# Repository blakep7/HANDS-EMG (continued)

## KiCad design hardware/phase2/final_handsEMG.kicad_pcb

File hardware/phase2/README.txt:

How to add components to our hands-emg-lib

1. Download the following from Ultra Librarian (https://app.ultralibrarian.com/)
	- Symbol (.kicad_sym)
	- Footprint (.kicad_mod) (Ignore the -L or -M footprints, use the normal one)
	- 3D Model (.stp or .step)
	* My typical download process
		* 3D CAD Model: Check STEP
		* KiCAD: Check KiCAD v6+
		* Symbol Pin Ordering: Designers preference, read the (i) to understand what this is.
		  Download both and compare to see which one would make a cleaner schematic.
		* Footprint Units: Metric (mm)
	
1b. If you cannot find the component on Ultra Librarian, check Component Search Engine (https://componentsearchengine.com/)
	- Don't mix and match symbols and footprints from different websites
	- If you cant find the components 3d model on ultralibrarian, its fine to download the 3d model from component search engine and attach to footprint from ultralibrarian.
	
1c. After downloading all the files it will be a zip do the following
	- Extract the zip to some folder on your PC.
	- Rename all the files to be the same name (typically part number)
	  Heres an example before and after with the ADS1299 from Ultra Librarian
			Before: 2025-03-01_06-35-12.kicad_sym
					PAG0064A.stp
					PAG64_TEX.kicad_mod
					
			After:  ADS1299-4PAGR.kicad_sym
					ADS1299-4PAGR.stp
					ADS1299-4PAGR.kicad_mod
	
2. Copy the 3d model file from the download into the hands-emg-lib.3dshapes.

3. Import the footprint
	- Open the KiCad Footprint Editor
	- Filter hands-emg-lib
	- Right click hands-emg-lib
	- Import Footprint
	- Select the footprint file from the download
	- Open the footprints properties menu
		- Check the "Value" and confirm its the proper manufacturer's part number (if you had to rename footprint file then it's likely incorrect)
		- Add a description of what it is (typically not part number, the description helps to search the part)
		- Go to the 3D model tab
		- Click the little folder icon to add 3d model
		- Select the 3d model file in the hands-emg-lib.3dshapes folder
		- Rotate/Offset model to fit the footprint (scaling is needed in very few cases)
	- Click OK to close the footprint properties menu
	- File -> Save
	- Dont change the name, filter for hands-emg-lib, click hands-emg-lib, click OK.
	
4. Import the symbol
	- Open the KiCad Symbol Editor
	- Filter hands-emg-lib
	- Right click hands-emg-lib
	- Import Symbol
	- Select the symbol file from the download
	- Open the symbol properties menu
		- Click on footprint
		- Click on the little books icon to open the "footprint chooser"
		- Filter for hands-emg-lib
		- Select the footprint imported in step 3 under hands-emg-lib (for this component)
		- Click OK
		- Add datasheet link under "Datasheet" field
		- Add description
		- Create new field
			- Click '+' symbol
			- Name this field procurement
			- Make sure to un-check the show column for this field
			- Provide purchase link for this component
				- Try to keep it all from DigiKey
				- No obsolete parts, no limited stock, must be immediately aviable, no lead time
		- Click OK to close symbol properties menu
	- File -> Save
	
5. Commit these changes to git and push so we all have easy access to the components.

6. Use your imported component. (Seach for hands-emg-lib in symbol/footprint selection menu when placing)

7. You can delete the downloaded files from your downloads folder, importing them has copied them all to our project.

Note! This library is 'project' scoped, there is no need to edit any of your kicad settings to use it. It will not be aviable in other projects.

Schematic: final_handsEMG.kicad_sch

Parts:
C1: 10uF; CAPC1608X90N
C2: 100uF; CAP_CC1206_YAG
C3, C9, C11, C26, C34: CKCL44X7R1H102M085AA; CAPCAF50P200X125X85-8; PARTREV Dec 2014
C5, C12, C13, C15, C24, C28: 0.1uF; YAG_CC0402_YAG
C6, C7, C14, C17, C18, C19, C21, C22, C27: 1uF; CAP_CC0402KRX7R5BB105_YAG
C16: 1nF; YAG_CC0402_YAG
C45, C46, C50, C51, C60, C61, C65, C66: 10uF; CAPC2012X95N
C47, C48, C49, C58, C62: 1uF; CAPC1608X90N
C57: 0.1uF; CAPC1608X90N
C59, C63, C64: 2.2uF; CAP_GRM18_MUR
C67: 0.01uF; CAPC1608X90N
D2, D3, D4, D5, D6, D7: TPD4E1B06DCKR; DCK6_TEX
J1: Conn_02x13_Odd_Even; AMPHENOL_68021-226HLF
L1, L2, L4, L5: 3.3uH; INDC2012X87N
R1, R2, R3, R4, R6: 2.2K; CAY16_BRN
R5: 1M; RC0402N_YAG
SWD1: FTSH-107-01-L-DV-K; CON14_2X7_DUK_FTSH_SAI
TP1: RAW; KEYSTONE_5000
TP2: LDO3V3; KEYSTONE_5000
TP4: +3V3; KEYSTONE_5000
TP5: -5V; KEYSTONE_5001
TP6: +5V; KEYSTONE_5001
TP7: +2V5; KEYSTONE_5001
TP8: -2V5; KEYSTONE_5001
U1: ADS1299CPAG; QFP64P50_1200X1200X120L60X22N
U2: STM32L496ZGT6; LQFP144-20x20mm_STM; PARTREV 10
U3: LTC3586EUFE-3-PBF; QFN-38_UFE_LIT
U4: FT231XQ-R; QFN20_FT231XQ_FTD
U6: TPS60403DBVT; SOT95P280X145-5N
U8: TPS72325DBVT; SOT95P280X145-5N
U9: TPS73225DBVT; SOT95P280X145-5N
dC1: 0.01uF; CC0402N_YAG
dC2, dC3: 47pF; G-033_MUR
dD3: D_Small; SOD882_STM
dD4: RED; LED_LTST-C191KRKT_LTO
dD5: GREEN; LED_LTST-C191KGKT_LTO
dF1: Fuse_Small; FUSE_F050-2
dL2: L_Small; IND_1005_TDK
dR1, dR2: 27; RC0402N_YAG
dR3, dR4: 330; RC0402N_YAG
dR6, dR7: 1K; RC0402N_YAG
pC1, pC4, pC5, pC8, pC9, pC11: 1uF; C1005X5R0J105M
pC2: 10uF; GRM21BR61A106KE19
pC3: 10uF; GRM21BR61A106KE19L
pC6, pC7, pC19: 22uF; JMK212BJ226MG-T
pC10: 2.2uF; C1608X5R0J225M
pC12, pC21, pC23: 10uF; C1608X5R0J106M
pC13: 100uF; GRM31CR60J107ME39L
pC14: 47uF; LMK316BJ476ML-T
pC15, pC20, pC22, pC24: 10pF; 04025A100KAT
pC16, pC28, pC29: 0.1uF; C1005X5R1C104K
pC17: 330pF; 04025A331KAT
pC18: 33pF; 04025A330KAT
pD2: GREEN (CHRG); LED-0603
pD3: RED (FAULT); LED-0603
pL1: 3.3uH; LPS4018-332MLC
pL2, pL3: 2.2uH; LPS4018-222MLC
pL4, pL5: 4.7uH; IND_LPS4018-472MRC
pQ1: PMOS; SI2333DS
pR2, pR29, pR30, pR31: 1; CRCW04021R00JNED
pR3, pR9: 100K; CRCW0402100KFKED
pR4, pR10, pR12: 0; CRCW04020000Z0EDC
pR5, pR7: 1K; CRCW04021K00JNED
pR6, pR8: 2.2K; CRCW04022K20FKED
pR13, pR18, pR23, pR26: 20; CRCW040220R0FKED
pR14: 88.7k; CRCW040288K7FKED
pR15: 16.9K; CRCW040216K9FKED
pR16: 3.01K; CRCW04023K01FKED
pR17: 2K; CRCW04022K00FKED
pR19: 15K; CRCW040215K0FKED
pR20: 324K; CRCW0402324KFKED
pR21: 121K; CRCW0402121KFKED
pR22: 105K; CRCW0402105KFKED
pR24: 806K; CRCW0402806KFKED
pR25: 649K; CRCW0402649KFKED
pR27: 232K; CRCW0402232KFKED
pR28: 464K; CRCW0402464KFKED
pR34, pR35, pR80, pR81, pR82, pR83: 10K; CRCW04021K00JNED
sB1: USER; PTS645S_SMTR92_CNK
sB2: RESET; PTS645S_SMTR92_CNK
sC28, sC29, sC30, sC31, sC32, sC33, sC34, sC49, sC50, sC51, sC53, sC57, sC58, sC61: 100nF; CAPC1608X90
sC40: [N/A]; YAG_CC0402_YAG
sC41: 100nF; YAG_CC0402_YAG
sC42: 4.7uF; CAPMP3216X166
sC52, sC54: 4.7uF_X54_0603; CAPC1608X90
sC56, sC59: 1uF; CAPMP3216X166
sC60: 1uF_X5R_0603; CAPC1608X90
sCN14: USB_B_Micro; MOLEX_47589-1001
sD6: ESDALC6V1_1U2; DIODE_ESDALC6V1-1U2
sD10: ESDALC6V1W5; SOT65P210X110-5N; MOUSER_PART_NUMBER 511-ESDALC6V1W5
sJ2: S2B-PH-K-SLFSN; CONN_S2B-PH-K-S_JST
sL3: FerriteBead_Small; FB0603
sLD7: Red; LED-0603
sLD8: Green; LED-0603
sR38, sR52: 10K; RESC1607X60N
sR41, sR43: 330; RESC1607X60N
sR42: 220K; RESC1607X60N
sR44: 100; RESC1607X60N
sR45: 620; RESC1608X55N
sR48: 22K; RESC1607X60N
sR49, sR51: 47K; RESC1608X55
sR54, sR55: 10K (DNP); RESC1607X60N
sT2: 9013; SOT-23
sU12: STMPS2151STR; SOT95P280X145-5N
sU13: USBLC6-2SC6; SOT-23-6

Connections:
1N: D3.4 (IO3), J1.21, R1.1
1P: D2.1 (IO1), J1.22, R1.2
2N: D3.2 (IO2), J1.19, R2.3
2P: D3.5 (IO4), J1.20, R2.4
3N: D4.4 (IO3), J1.17, R2.1
3P: D3.1 (IO1), J1.18, R2.2
3V3OUT: U4.10 (3V3OUT), U4.11 (RESET#), dD4.2 (A), dD5.2 (A)
4N: D4.2 (IO2), J1.15, R3.3
4P: D4.5 (IO4), J1.16, R3.4
5N: D5.4 (IO3), J1.13, R3.1
5P: D4.1 (IO1), J1.14, R3.2
5VCC: C45.1, C46.1, C47.1, C58.1, L1.1, L1.2, TP6.1, U3.6 (VOUT4), U3.7 (VOUT4), U6.2 (IN), U9.1 (IN), U9.3 (EN), pC14.1, pR13.2
6N: D5.2 (IO2), J1.11, R4.3
6P: D5.5 (IO4), J1.12, R4.4
7N: D6.4 (IO3), J1.9, R4.1
7P: D5.1 (IO1), J1.10, R4.2
8N: D6.2 (IO2), J1.7, R6.3
8P: D6.5 (IO4), J1.8, R6.4
*CHRG: U3.30 (*CHRG), pR5.2, pR6.2
*FAULT: U3.38 (*FAULT), pR7.2, pR8.2, pR80.2
-5VCC: C49.1, C50.1, C51.1, C63.1, L2.1, L2.2, TP5.1, U6.1 (OUT), U8.2 (IN), U8.3 (EN)
AVBUS: U3.35 (VBUS), U3.36 (VBUS), dD3.1 (K), dF1.2, pC2.1, pC3.1, pC8.1, pR3.1, sC42.+, sR49.2, sR54.2, sU12.1 (OUT), sU13.5 (VBUS)
AVDD: C13.1, C17.1, C22.1, C24.1, C27.1, C28.1, C57.1, C61.1, D7.2 (IO2), J1.1, J1.2, L5.2, TP7.1, U1.19 (AVDD@1), U1.21 (AVDD@1), U1.22 (AVDD@1), U1.54 (AVDD1), U1.56 (AVDD@1), U1.59 (AVDD@2), U2.32 (VREF+), U2.33 (VDDA), sC56.+, sC57.1, sC58.1, sC59.+, sL3.2
AVIN3: U3.14 (VIN3), pC11.1, pR4.1
AVOUT3: C12.1, C14.1, SWD1.3, TP4.1, U1.48 (DVDD), U1.50 (DVDD), U2.6 (VBAT), U2.17 (VDD), U2.39 (VDD__1), U2.52 (VDD__2), U2.62 (VDD__3), U2.72 (VDD__4), U2.84 (VDD__5), U2.95 (VDDIO2), U2.106 (VDDUSB), U2.108 (VDD__6), U2.121 (VDD__7), U2.131 (VDDIO2__1), U2.144 (VDD__8), U3.16 (VOUT3), U3.17 (VOUT3), U4.12 (VCC), U4.20 (VCCIO), pC19.1, pR18.1, sB1.2, sB1.3, sC28.1, sC29.1, sC30.1, sC31.1, sC32.1, sC33.1, sC34.1, sC49.1, sC50.1, sC51.1, sC52.1, sC53.1, sC54.1, sC60.1, sC61.1, sL3.1, sR41.2, sR44.1, sR45.2, sR51.2, sU12.5 (IN)
AVSS: C1.2, C2.2, C5.2, C6.2, C7.2, C13.2, C15.2, C17.2, C18.1, C19.2, C21.1, C57.2, C66.1, D2.4 (IO3), J1.25, J1.26, L4.2, TP8.1, U1.20 (AVSS@1), U1.23 (AVSS@1), U1.25 (VREFN), U1.32 (AVSS@1), U1.53 (AVSS1), U1.57 (AVSS@1), U1.58 (AVSS@2)
BAT: TP1.1, U3.32 (BAT), pC13.1, pQ1.1 (D), sJ2.1; also elsewhere on the board
BIAS: D7.4 (IO3), J1.5, J1.6, R6.1
BIASIN: C16.2, R5.2, U1.62 (BIASIN), U1.63 (BIASOUT)
BIASINV: U1.61 (BIASINV)
BIASREF: U1.60 (BIASREF)
BIAS_DRV: C16.1, C34.5, R5.1, R6.8
CBUS1: U4.14 (CBUS1), dR4.2
CBUS2: U4.7 (CBUS2), dR3.1
CLK: U1.37 (CLK)
CLKSEL: U1.52 (CLKSEL)
CLPROG: U3.4 (CLPROG), pC16.1, pR16.1
DAISY_IN: U1.41 (DAISY_IN)
DGND: C45.2, C46.2, C47.2, C49.2, C50.2, C51.2, C58.2, C59.2, C60.2, C61.2, C62.2, C63.2, C64.2, C65.2, C66.2, C67.2, SWD1.5, SWD1.7, U1.33 (DGND), U1.49 (DGND), U1.51 (DGND), U2.16 (VSS), U2.30 (VSSA/VREF-), U2.31 (VREF-), U2.38 (VSS__1), U2.51 (VSS__2), U2.61 (VSS__3), U2.71 (VSS__4), U2.83 (VSS__5), U2.94 (VSS__6), U2.107 (VSS__7), U2.120 (VSS__8), U2.130 (VSS__9), U2.143 (VSS__10), U3.39 (EPAD), U4.3 (GND), U4.13 (GND), U4.21 (GND), U6.4 (GND), U8.1 (GND), U9.2 (GND), dC1.2, dC2.2, dC3.2, dD3.2 (A), pC1.2, pC3.2, pC4.2, pC5.2, pC6.2, pC7.2, pC8.2, pC9.2, pC10.2, pC11.2, pC12.2, pC14.2, pC16.2, pC19.2, pC21.1, pC23.1, pC28.2, pC29.2, pR2.2, pR9.1, pR15.1, pR16.2, pR17.2, pR22.2, pR25.2, pR28.2, pR29.1, pR30.1, pR31.1, sB2.2, sB2.3, sC28.2, sC29.2, sC30.2, sC31.2, sC32.2, sC33.2, sC34.2, sC41.2, sC42.-, sC49.2, sC50.2, sC51.2, sC52.2, sC53.2, sC54.2, sC56.-, sC57.2, sC58.2, sC59.-, sC60.2, sC61.2, sCN14.5 (GND), sD6.2 (A), sD10.2 (GND), sJ2.2, sR38.2, sR42.1, sR48.1, sR52.2, sT2.2 (E), sU12.2 (GND), sU13.2 (GND); also elsewhere on the board
DIN: U1.34 (DIN), U2.43 (PA7)
DOUT: U1.43 (DOUT), U2.42 (PA6)
EN1: U2.115 (PD1), U3.21 (EN1)
EN2: U2.116 (PD2), U3.20 (EN2)
EN3: U2.117 (PD3), U3.18 (EN3), pC28.1, pR34.1
EN4: U2.118 (PD4), U3.33 (EN4), pC29.1, pR35.1
FB1: U3.28 (FB1), pC24.1, pR27.2, pR28.1
FB2: U3.23 (FB2), pC22.1, pR24.2, pR25.1
FB3: U3.11 (FB3), pC20.2, pR19.2, pR20.2, pR21.2, pR22.1
FB4: U3.10 (FB4), pC15.2, pR14.1, pR15.2
GATE: U3.31 (GATE), pQ1.2 (G)
GNDA: C3.1, C3.2, C3.3, C3.4, C9.1, C9.2, C9.3, C9.4, C11.1, C11.2, C11.3, C11.4, C12.2, C14.2, C18.2, C21.2, C22.2, C24.2, C26.1, C26.2, C26.3, C26.4, C27.2, C28.2, C34.1, C34.2, C34.3, C34.4, C34.6, D2.3 (GND), D3.3 (GND), D4.3 (GND), D5.3 (GND), D6.3 (GND), D7.1 (IO1), D7.3 (GND), J1.3, J1.4, R6.2, R6.7
GPIO1: U1.42 (GPIO1)
GPIO2: U1.44 (GPIO2)
GPIO3: U1.45 (GPIO3)
GPIO4: U1.46 (GPIO4)
ILIM0: U3.1 (ILIM0), pR81.2
ILIM1: U3.2 (ILIM1), pR82.2
IN1N: C3.5, R1.8, U1.15 (IN1N)
IN1P: C3.6, R1.7, U1.16 (IN1P)
IN2N: C9.7, R2.6, U1.13 (IN2N)
IN2P: C9.8, R2.5, U1.14 (IN2P)
IN3N: C9.5, R2.8, U1.11 (IN3N)
IN3P: C9.6, R2.7, U1.12 (IN3P)
IN4N: C11.7, R3.6, U1.9 (IN4N)
IN4P: C11.8, R3.5, U1.10 (IN4P)
IN5N: C11.5, R3.8, U1.7 (IN5N)
IN5P: C11.6, R3.7, U1.8 (IN5P)
IN6N: C26.7, R4.6, U1.5 (IN6N)
IN6P: C26.8, R4.5, U1.6 (IN6P)
IN7N: C26.5, R4.8, U1.3 (IN7N)
IN7P: C26.6, R4.7, U1.4 (IN7P)
IN8N: C34.7, R6.6, U1.1 (IN8N)
IN8P: C34.8, R6.5, U1.2 (IN8P)
LDO3V3: TP2.1, U3.3 (LDO3V3), pC1.1, pD2.+ (A), pD3.+ (A), pR6.1, pR8.1, pR12.2, pR34.2, pR35.2
MODE: U3.9 (MODE), pR83.2
NRST: SWD1.12, U2.25 (~NRST), sB2.1, sB2.4, sC41.1, sD10.3 (I/02)
NTC: U3.5 (NTC), pR3.2, pR10.2
unnamed: U2.138 (PH3-BOOT0), sR38.1
unnamed: U4.1 (RXD), dR6.2
unnamed: U4.17 (TXD), dR7.2
unnamed: C48.1, U6.5 (CFLY+)
unnamed: C48.2, U6.3 (CFLY-)
unnamed: C67.1, U8.4 (NR)
unnamed: C64.1, C65.1, L4.1, U8.5 (OUT)
unnamed: C62.1, U9.4 (NR/FB)
unnamed: C59.1, C60.1, L5.1, U9.5 (OUT)
unnamed: dD4.1 (K), dR3.2
unnamed: dD5.1 (K), dR4.1
unnamed: dF1.1, dL2.2
unnamed: pC2.2, pR2.1
unnamed: pC13.2, pR29.2, pR30.2, pR31.2
unnamed: pC15.1, pR13.1, pR14.2
unnamed: pC17.2, pR19.1
unnamed: pC18.1, pR18.2, pR20.1
unnamed: pC18.2, pR21.1
unnamed: pC22.2, pR23.2, pR24.1
unnamed: pC24.2, pR26.2, pR27.1
unnamed: pD2.- (K), pR5.1
unnamed: pD3.- (K), pR7.1
unnamed: pR9.2, pR10.1
unnamed: sB1.1, sB1.4, sC40.1, sR42.2, sR43.2
unnamed: sC40.2, sR44.2
unnamed: dC3.1, dR1.1, sCN14.3 (D+)
unnamed: dC2.1, dR2.1, sCN14.2 (D-)
unnamed: dC1.1, dL2.1, sCN14.1 (VBUS)
unnamed: sLD7.+ (A), sR45.1
unnamed: sLD7.- (K), sR51.1, sU12.3 (FAULT)
unnamed: sLD8.+ (A), sR41.1
unnamed: sLD8.- (K), sT2.3 (C)
unnamed: sR48.2, sR49.1, sT2.1 (B)
unnamed: sR52.1, sU12.4 (EN)
PA1: U1.40 (SCLK), U2.35 (PA1)
PA4: U1.39 (~CS), U2.40 (PA4)
PA5: U1.47 (~DRDY), U2.41 (PA5)
PA8: U2.100 (PA8)
PA9: U2.101 (PA9), sR54.1
PA10: U2.102 (PA10), sR55.1
PA11: U2.103 (PA11)
PA12: U2.104 (PA12)
PA13: SWD1.4, U2.105 (PA13(JTMS/SWDIO)), sD10.4 (I/03)
PA14: SWD1.6, U2.109 (PA14(JTCK/SWCLK)), sD10.5 (I/04)
PB0: U1.38 (START), U2.46 (PB0)
PB3: SWD1.8, U2.133 (PB3(JTDO/TRACESWO)), sD10.1 (I/01)
PB7: U2.137 (PB7)
PB12: U2.73 (PB12)
PB13: U2.74 (PB13)
PB14: U2.75 (PB14)
PB15: U2.76 (PB15)
PC4: U1.35 (~PWDN), U2.44 (PC4)
PC5: U1.36 (~RESET), U2.45 (PC5)
PC7: U2.97 (PC7)
PC10: U2.111 (PC10), pR83.1
PC11: U2.112 (PC11), pR82.1
PC12: U2.113 (PC12), pR81.1
PC13: U2.7 (PC13), sR43.1
PD0: U2.114 (PD0), pR80.1
PD5: U2.119 (PD5), dR6.1
PD6: U2.122 (PD6), dR7.1
PD8: U2.77 (PD8)
PD9: U2.78 (PD9)
PD10: U2.79 (PD10)
PD11: U2.80 (PD11)
PD12: U2.81 (PD12)
PD13: U2.82 (PD13)
PG13: U2.128 (PG13)
PG14: U2.129 (PG14)
PROG: U3.29 (PROG), pR17.1
PVIN3: U3.15 (VIN3), U3.22 (VIN4), U3.24 (VIN2), U3.27 (VIN1), U3.34 (VOUT), pC4.1, pC5.1, pC6.1, pC7.1, pC9.1, pC10.1, pC12.1, pL1.2, pL2.2, pQ1.3 (S), pR4.2, pR12.1
RESERVED: U1.64 (RESERVED)
RESV1: U1.31 (RESV1)
SRB1: D2.5 (IO4), J1.24, R1.4
SRB2: D2.2 (IO2), J1.23, R1.3
SW: U3.37 (SW), pL1.1
SW1: U3.26 (SW1), pL5.1
SW2: U3.25 (SW2), pL4.1
SW4: U3.8 (SW4), pL2.1
SWAB3: U3.13 (SWAB3), pL3.2
SWCD3: U3.19 (SWCD3), pL3.1
USB_DN: U4.9 (USBDM), dR2.2, sU13.1 (I/O1), sU13.6 (I/O1)
USB_DP: U4.8 (USBDP), dR1.2, sU13.3 (I/O2), sU13.4 (I/O2)
USB_ID: sCN14.4 (ID), sD6.1 (K), sR55.2
VC3: U3.12 (VC3), pC17.1, pC20.1
VCAP1: C2.1, U1.28 (VCAP1)
VCAP2: C7.1, U1.30 (VCAP2)
VCAP3: C15.1, C19.1, U1.55 (VCAP3)
VCAP4: C6.1, U1.26 (VCAP4)
VOUT1: pC23.2, pL5.2, pR26.1
VOUT2: pC21.2, pL4.2, pR23.1
VREFP: C1.1, C5.1, U1.24 (VREFP)
_SRB1: C3.8, R1.5, U1.17 (SRB1)
_SRB2: C3.7, R1.6, U1.18 (SRB2)

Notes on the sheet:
ADS1299
FT231XQ-R
LTC3586
STM32L496ZGT6

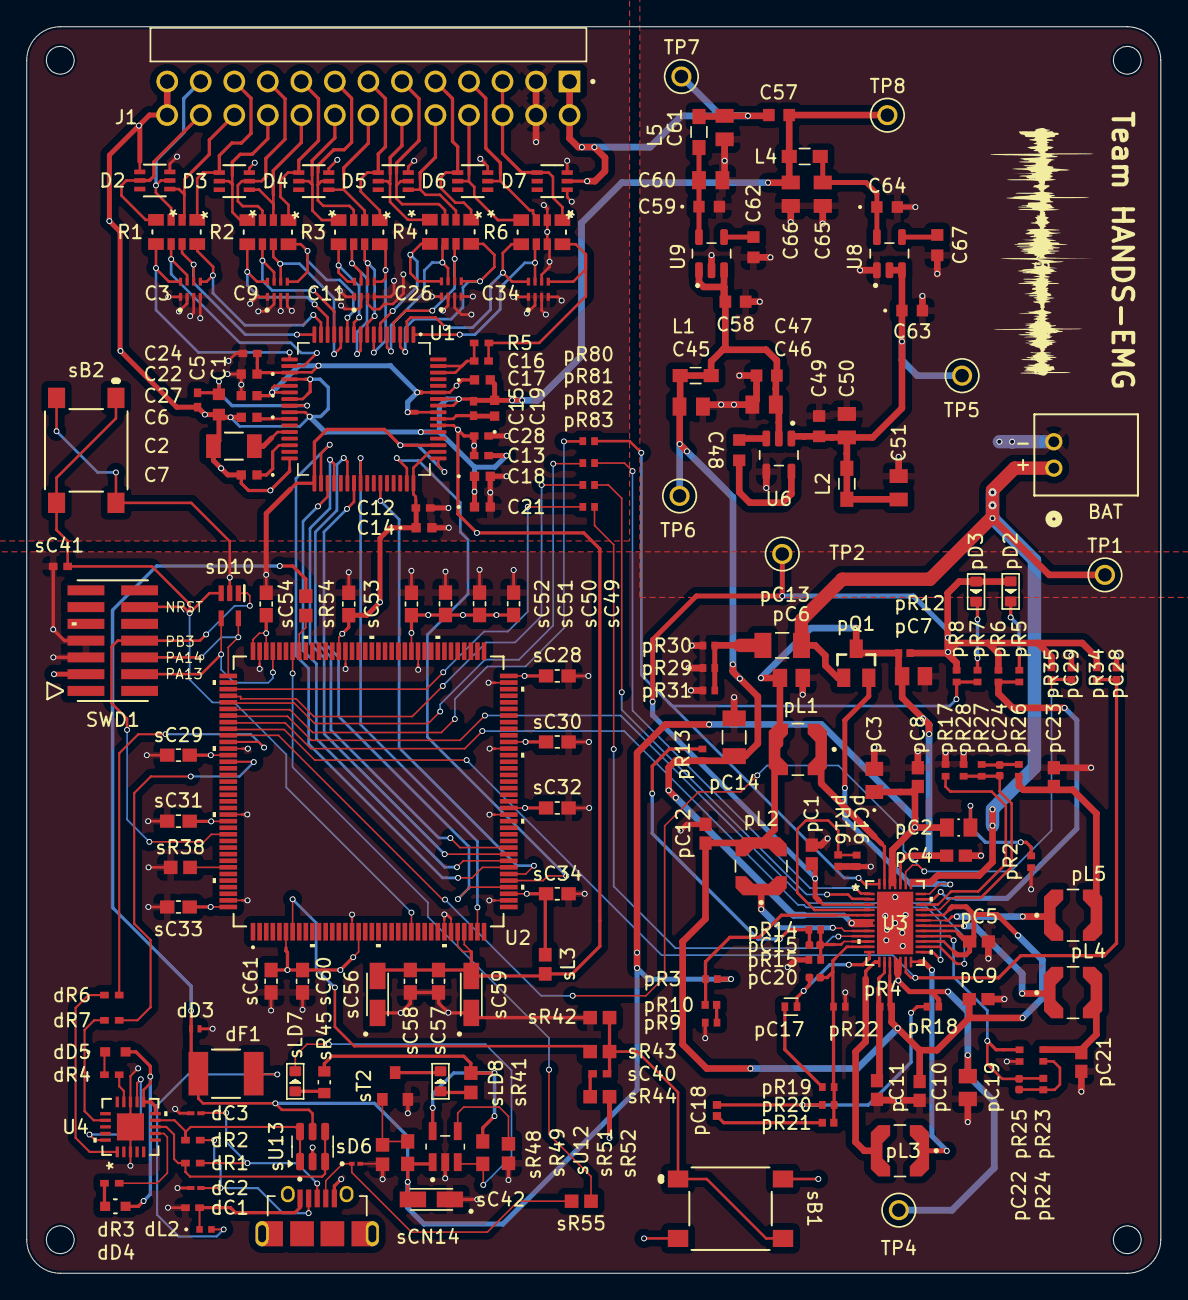
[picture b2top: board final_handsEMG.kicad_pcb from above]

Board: 4 copper layers, 85.9 x 94.4 mm, 202 parts (0 on the bottom side), 143 nets.

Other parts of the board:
BAT: S2B-PH-K-SLFSN; CONN_S2B-PH-K-S_JST

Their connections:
BAT: BAT.1; also elsewhere on the board
DGND: BAT.2; also elsewhere on the board

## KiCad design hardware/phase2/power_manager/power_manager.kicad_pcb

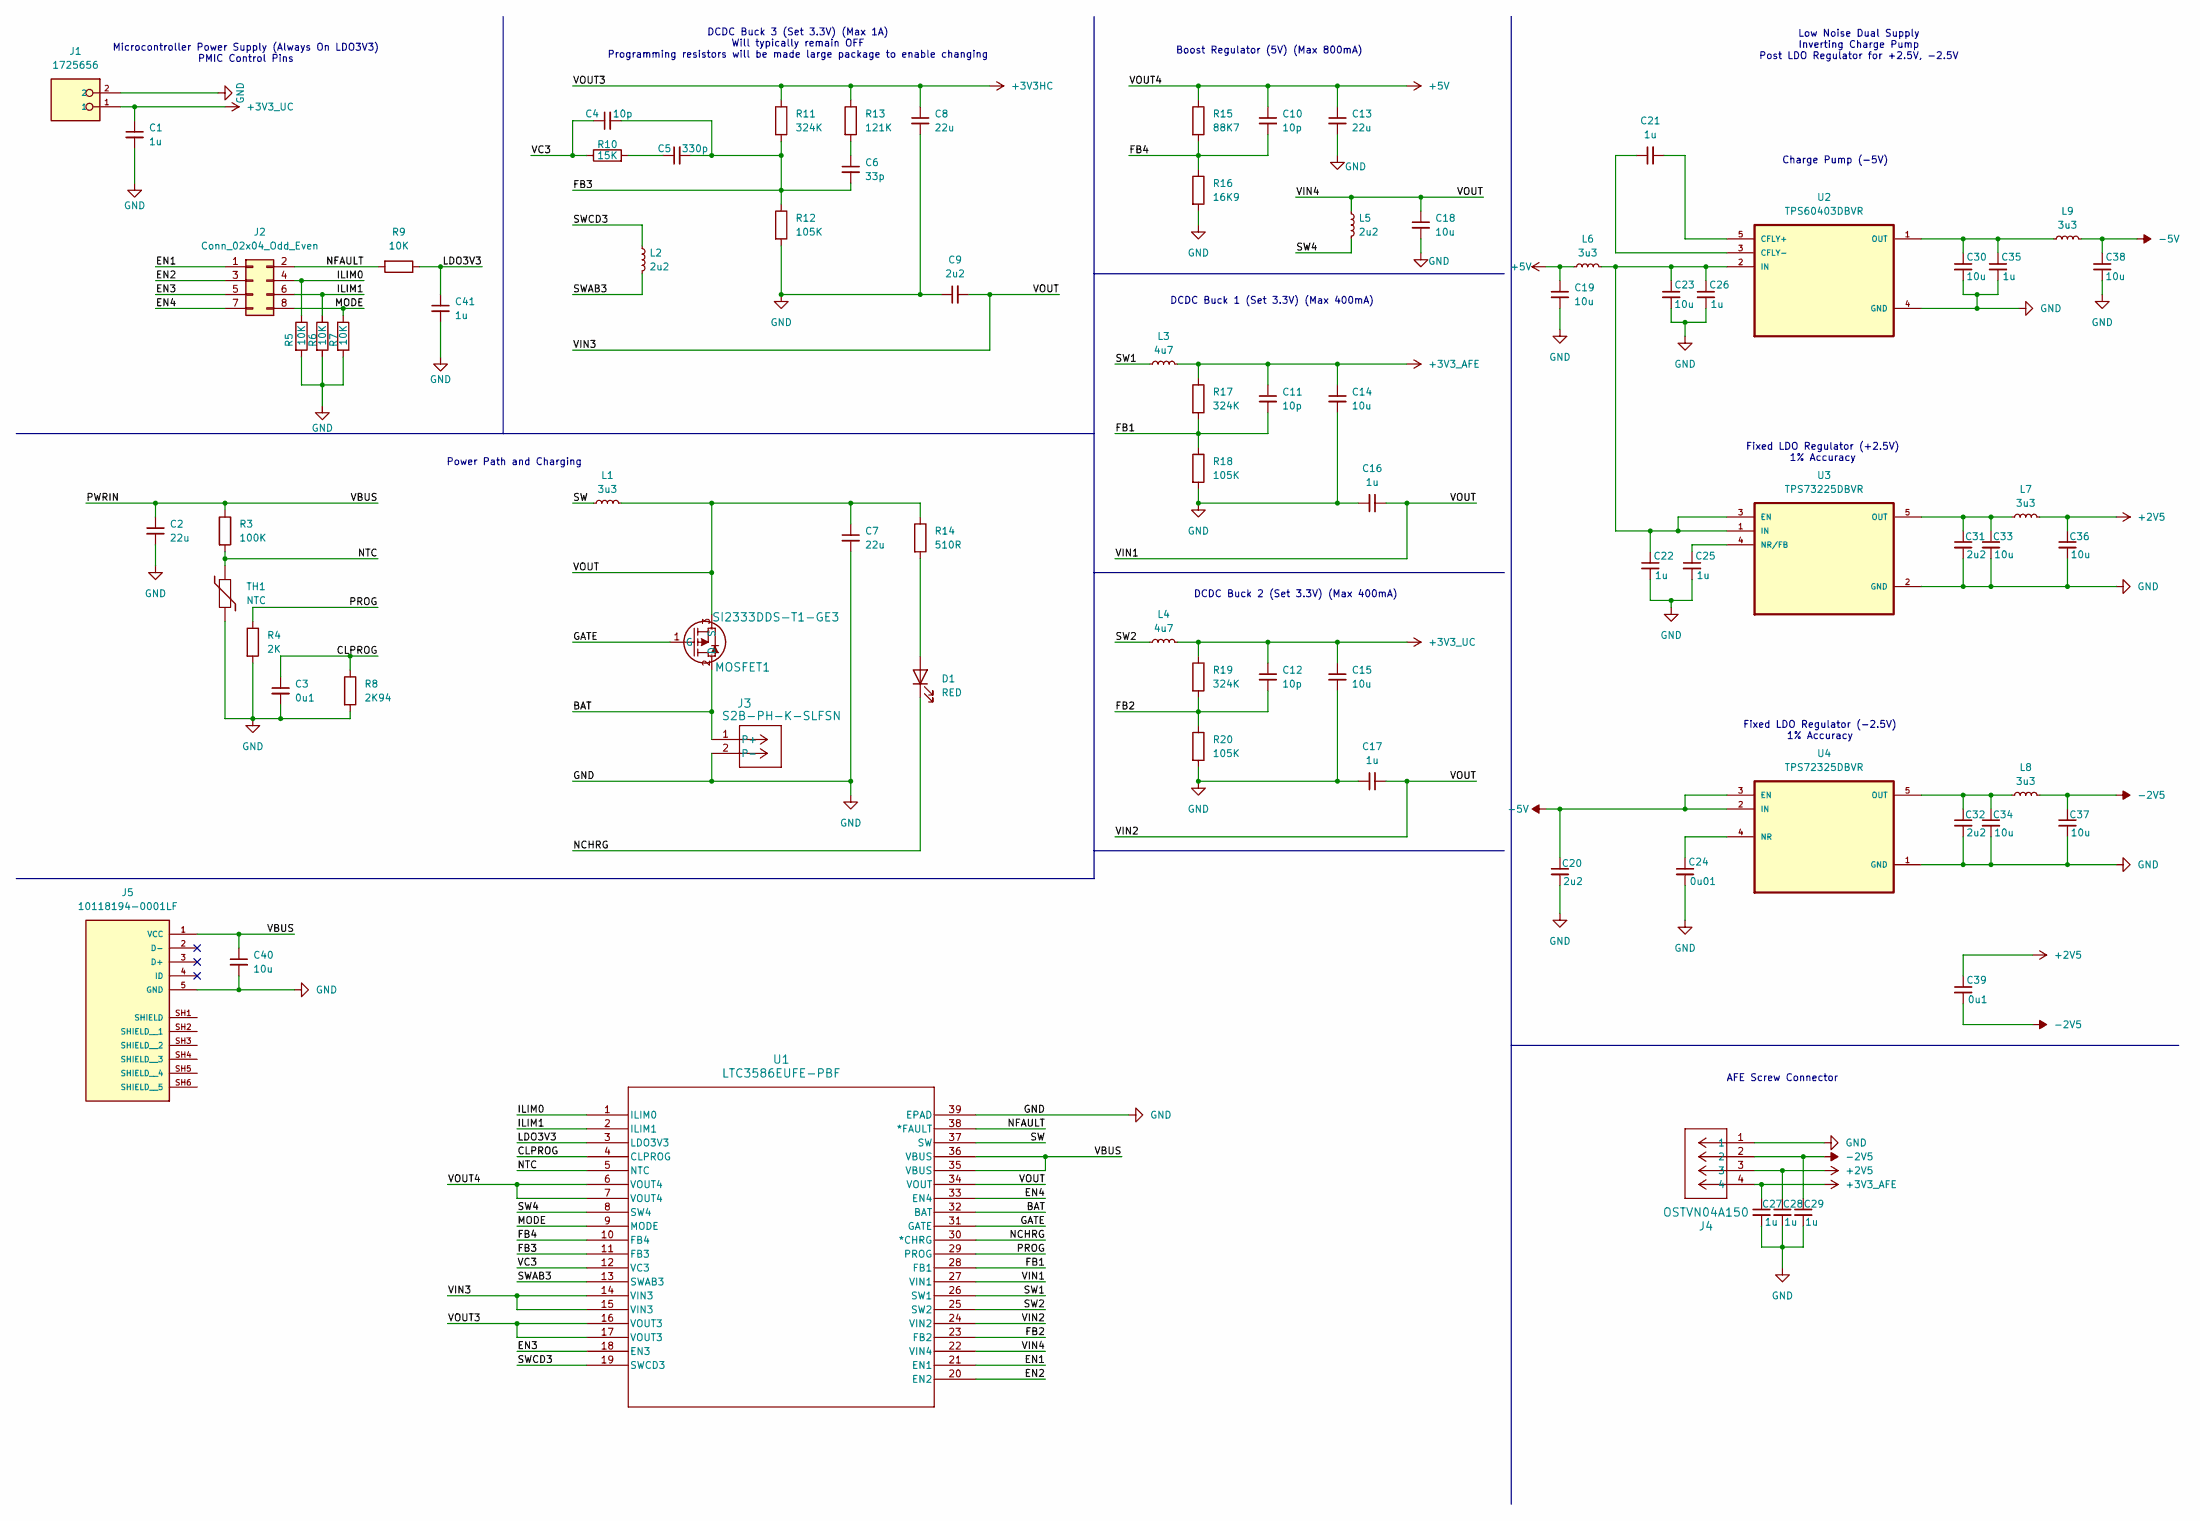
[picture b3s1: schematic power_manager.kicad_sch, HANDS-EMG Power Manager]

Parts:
C1, C16, C17, C27, C28, C29, C41: 1u; C_0402_1005Metric
C2, C7, C8, C13: 22u; C_0805_2012Metric
C3: 0u1; C_0402_1005Metric
C4, C11, C12: 10p; C_0402_1005Metric
C5: 330p; C_0402_1005Metric
C6: 33p; C_0402_1005Metric
C9: 2u2; C_0402_1005Metric
C10: 10p; C_0603_1608Metric
C14, C15, C18: 10u; C_0603_1608Metric
C19, C23, C30, C33, C34, C36, C37, C38, C40: 10u; C_0805_2012Metric
C20, C31, C32: 2u2; C_0603_1608Metric
C21, C22, C25, C26, C35: 1u; C_0603_1608Metric
C24: 0u01; C_0603_1608Metric
C39: 0u1; C_0603_1608Metric
D1: RED; LED_1210_3225Metric
J1: 1725656; PARTREV 03.03.2021
J2: Conn_02x04_Odd_Even; PinSocket_2x04_P2.54mm_Vertical
J3: S2B-PH-K-SLFSN; S2B-PH-K-S
J4: OSTVN04A150
J5: 10118194-0001LF; PARTREV D
L1: 3u3; L_Coilcraft_LPS4018
L2, L5: 2u2; L_Coilcraft_LPS4018
L3, L4: 4u7; L_Coilcraft_LPS3010
L6, L7, L8, L9: 3u3; L_0805_2012Metric
MOSFET1: SI2333DDS-T1-GE3
R3: 100K; R_0402_1005Metric
R4: 2K; R_0402_1005Metric
R5, R6, R7, R9: 10K; R_0603_1608Metric
R8: 2K94; R_0402_1005Metric
R10: 15K; R_0402_1005Metric
R11, R17, R19: 324K; R_0402_1005Metric
R12, R18, R20: 105K; R_0402_1005Metric
R13: 121K; R_0402_1005Metric
R14: 510R; R_0402_1005Metric
R15: 88K7; R_0603_1608Metric
R16: 16K9; R_0603_1608Metric
TH1: NTC; R_Axial_DIN0204_L3.6mm_D1.6mm_P2.54mm_Vertical
U1: LTC3586EUFE-PBF; LTC3586EUFE_PBF
U2: TPS60403DBVR
U3: TPS73225DBVR
U4: TPS72325DBVR

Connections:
+2V5: C28.1, C36.1, C39.1, J4.3, L7.2
+3V3HC: C8.1, R11.1, R13.1, U1.16 (VOUT3), U1.17 (VOUT3)
+3V3_AFE: C11.1, C14.1, C27.1, J4.4, L3.2, R17.1
+3V3_UC: C1.1, C12.1, C15.1, J1.1, L4.2, R19.1
+5V: C10.1, C13.1, C19.1, L6.1, R15.1, U1.6 (VOUT4), U1.7 (VOUT4)
-2V5: C29.1, C37.1, C39.2, J4.2, L8.2
-5V: C20.1, C38.1, L9.2, U4.2 (IN), U4.3 (EN)
/BAT: J3.1 (P+), MOSFET1.2 (D), U1.32 (BAT)
/CLPROG: C3.1, R8.1, U1.4 (CLPROG)
/EN1: J2.1, U1.21 (EN1)
/EN2: J2.3, U1.20 (EN2)
/EN3: J2.5, U1.18 (EN3)
/EN4: J2.7, U1.33 (EN4)
/FB1: C11.2, R17.2, R18.1, U1.28 (FB1)
/FB2: C12.2, R19.2, R20.1, U1.23 (FB2)
/FB3: C4.2, C5.2, C6.2, R11.2, R12.1, U1.11 (FB3)
/FB4: C10.2, R15.2, R16.1, U1.10 (FB4)
/GATE: MOSFET1.1 (G), U1.31 (GATE)
/ILIM0: J2.4, R5.1, U1.1 (ILIM0)
/ILIM1: J2.6, R6.1, U1.2 (ILIM1)
/LDO3V3: C41.1, R9.1, U1.3 (LDO3V3)
/MODE: J2.8, R7.1, U1.9 (MODE)
/NCHRG: D1.1 (K), U1.30 (*CHRG)
/NFAULT: J2.2, R9.2, U1.38 (*FAULT)
/NTC: R3.2, TH1.1, U1.5 (NTC)
/PROG: R4.1, U1.29 (PROG)
/PWRIN: C2.1, C40.1, J5.1 (VCC), R3.1, U1.35 (VBUS), U1.36 (VBUS)
/SW: L1.1, U1.37 (SW)
/SW1: L3.1, U1.26 (SW1)
/SW2: L4.1, U1.25 (SW2)
/SW4: L5.2, U1.8 (SW4)
/SWAB3: L2.2, U1.13 (SWAB3)
/SWCD3: L2.1, U1.19 (SWCD3)
/VC3: C4.1, R10.1, U1.12 (VC3)
/VIN1: C7.1, C9.2, C16.2, C17.2, C18.1, L1.2, L5.1, MOSFET1.3 (S), R14.1, U1.14 (VIN3), U1.15 (VIN3), U1.22 (VIN4), U1.24 (VIN2), U1.27 (VIN1), U1.34 (VOUT)
GND: C1.2, C2.2, C3.2, C7.2, C8.2, C9.1, C13.2, C14.2, C15.2, C16.1, C17.1, C18.2, C19.2, C20.2, C22.2, C23.2, C24.2, C25.2, C26.2, C27.2, C28.2, C29.2, C30.2, C31.2, C32.2, C33.2, C34.2, C35.2, C36.2, C37.2, C38.2, C40.2, C41.2, J1.2, J3.2 (P-), J4.1, J5.5 (GND), R4.2, R5.2, R6.2, R7.2, R8.2, R12.2, R16.2, R18.2, R20.2, TH1.2, U1.39 (EPAD), U2.4 (GND), U3.2 (GND), U4.1 (GND)
unnamed: C5.1, R10.2
unnamed: C6.1, R13.2
unnamed: D1.2 (A), R14.2
unnamed: C21.2, U2.5 (CFLY+)
unnamed: C21.1, U2.3 (CFLY-)
unnamed: C22.1, C23.1, C26.1, L6.2, U2.2 (IN), U3.1 (IN), U3.3 (EN)
unnamed: C30.1, C35.1, L9.1, U2.1 (OUT)
unnamed: C25.1, U3.4 (NR/FB)
unnamed: C31.1, C33.1, L7.1, U3.5 (OUT)
unnamed: C24.1, U4.4 (NR)
unnamed: C32.1, C34.1, L8.1, U4.5 (OUT)

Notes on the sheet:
DCDC Buck 2 (Set 3.3V) (Max 400mA)
Boost Regulator (5V) (Max 800mA)
Low Noise Dual Supply Inverting Charge Pump Post LDO Regulator for +2.5V, -2.5V
Fixed LDO Regulator (+2.5V) 1% Accuracy
Charge Pump (-5V)
Fixed LDO Regulator (-2.5V) 1% Accuracy
AFE Screw Connector
Power Path and Charging
DCDC Buck 3 (Set 3.3V) (Max 1A) Will typically remain OFF Programming resistors will be made large package to enable changing
Microcontroller Power Supply (Always On LDO3V3) PMIC Control Pins
DCDC Buck 1 (Set 3.3V) (Max 400mA)

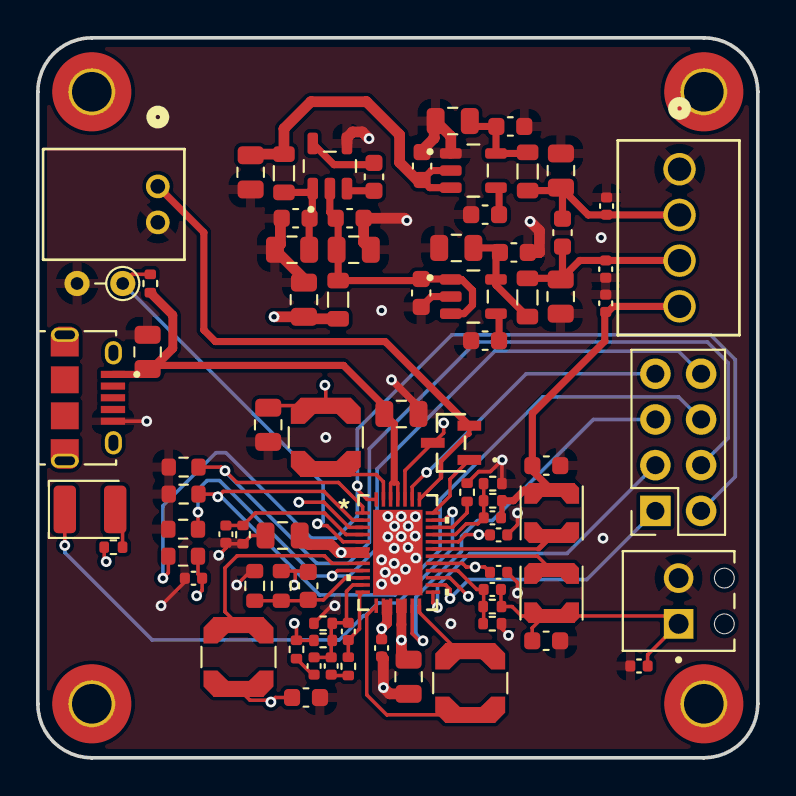
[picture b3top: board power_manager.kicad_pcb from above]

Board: 4 copper layers, 40.0 x 40.0 mm, 80 parts (0 on the bottom side), 47 nets.

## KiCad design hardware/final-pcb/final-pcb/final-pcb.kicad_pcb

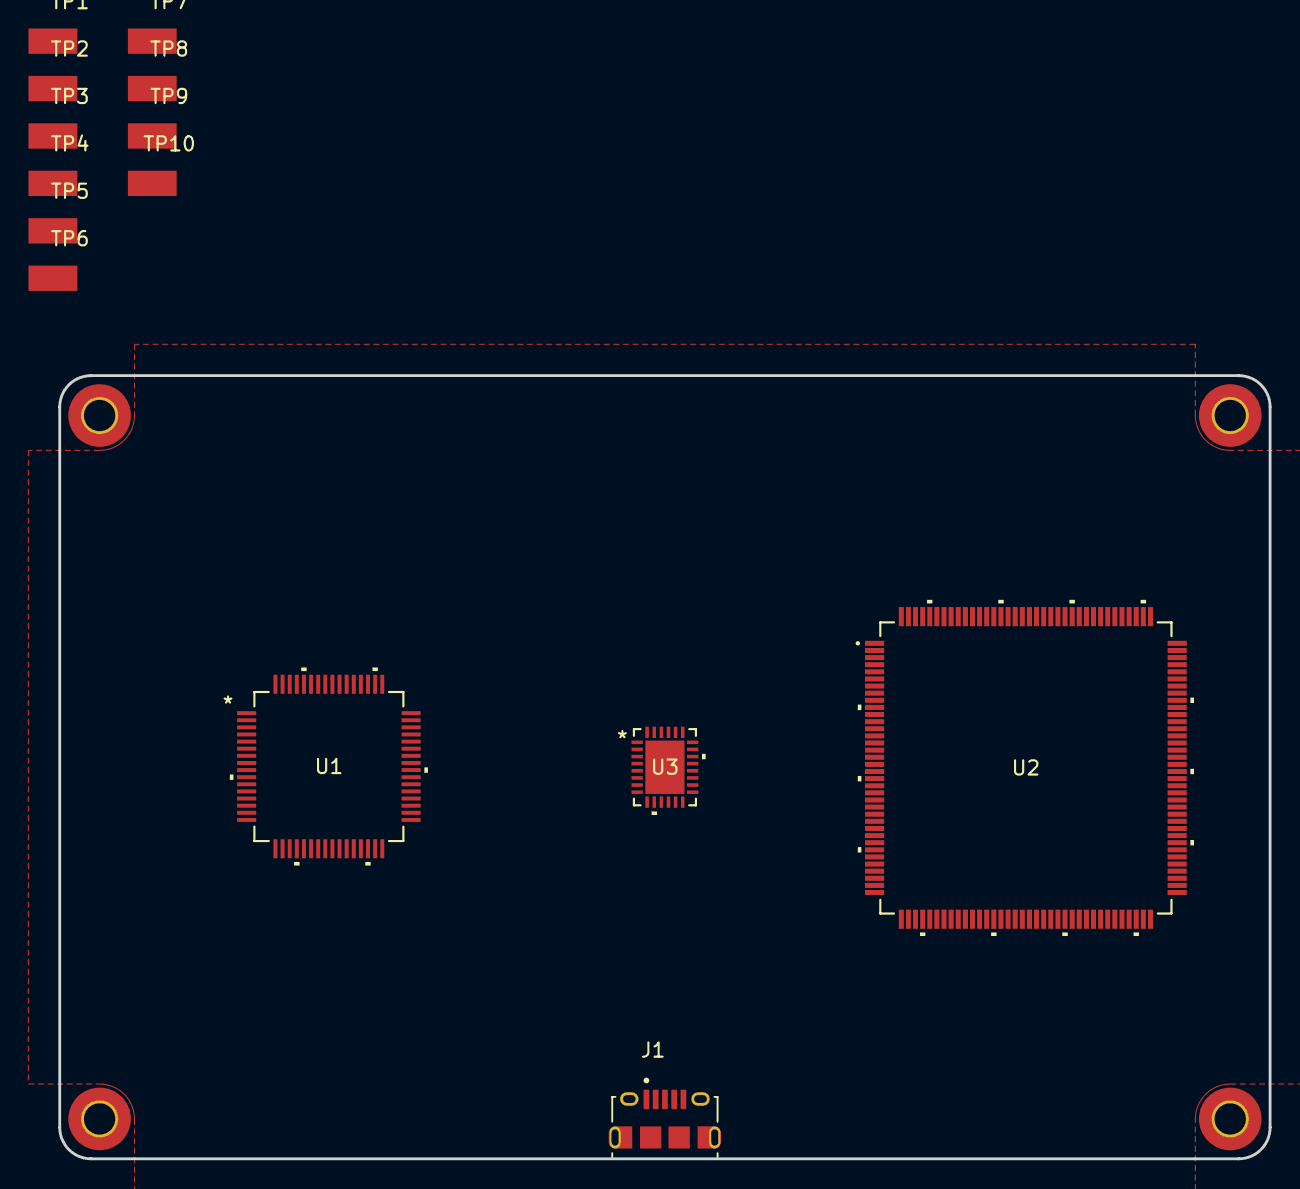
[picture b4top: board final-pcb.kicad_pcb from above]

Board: 4 copper layers, 85.0 x 55.0 mm, 14 parts (0 on the bottom side), 5 nets, no tracks yet.

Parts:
J1: 10118194-0001LF
TP1, TP2, TP3, TP4, TP5, TP6, TP7, TP8, TP9, TP10: KEYSTONE_5015
U1: ADS1299-4PAGR
U2: STM32L496ZGT6
U3: LTC3556EUFD-PBF

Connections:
GNDD: J1.5 (GND), TP10.TP, U2.16 (VSS), U2.30 (VSSA), U2.38 (VSS), U2.51 (VSS), U2.61 (VSS), U2.71 (VSS), U2.83 (VSS), U2.94 (VSS), U2.107 (VSS), U2.120 (VSS), U2.130 (VSS), U2.143 (VSS)
SPI_MISO: TP2.TP, U1.43 (DOUT)
SPI_MOSI: TP1.TP, U1.34 (DIN)
SPI_NSS: TP3.TP, U1.39 (*CS)
SPI_SCK: TP4.TP, U1.40 (SCLK)
